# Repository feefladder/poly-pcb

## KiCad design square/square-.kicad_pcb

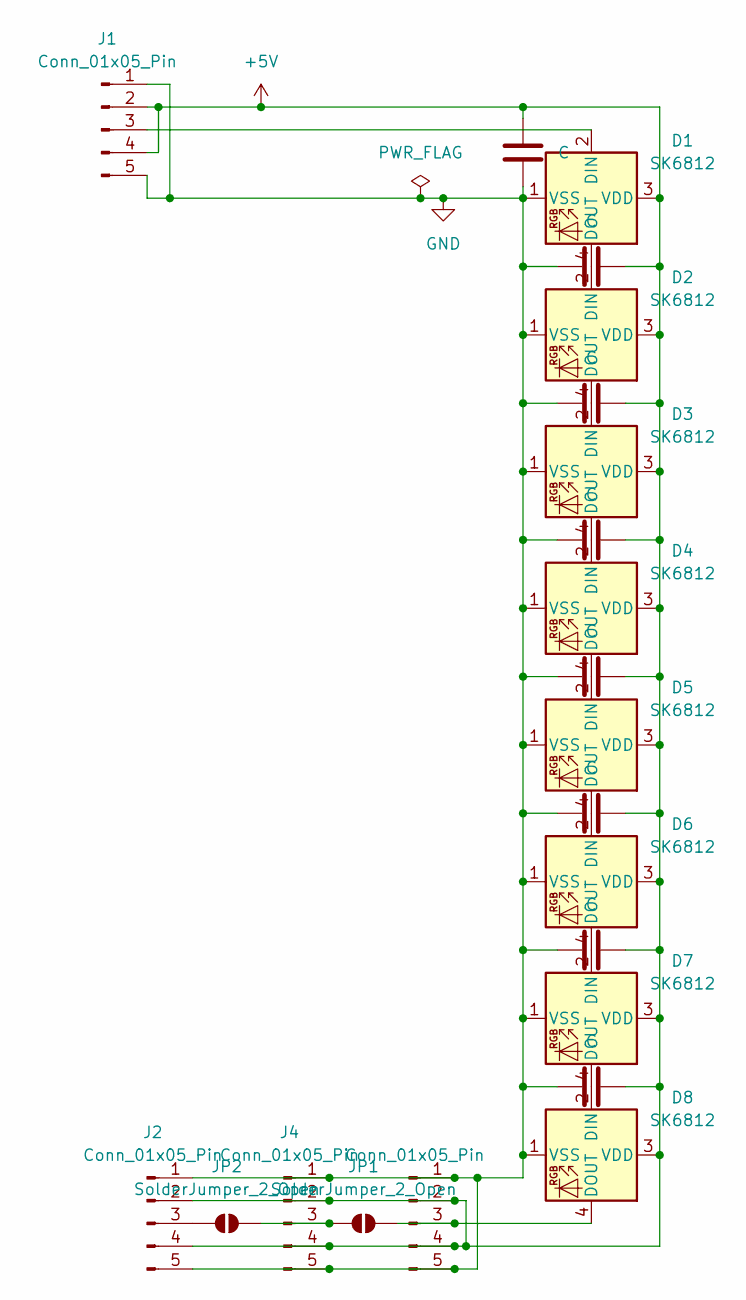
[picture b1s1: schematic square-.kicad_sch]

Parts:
C1, C2, C3, C4, C5, C6, C7, C8: C; C_0805_2012Metric_Pad1.18x1.45mm_HandSolder
D1, D2, D3, D4, D5, D6, D7, D8: SK6812; LED_SK6812_PLCC4_5.0x5.0mm_P3.2mm
J1, J2, J3, J4: Conn_01x05_Pin; PinHeader_1x05_P2.54mm_Vertical
JP1, JP2: SolderJumper_2_Open; SolderJumper-2_P1.3mm_Open_Pad1.0x1.5mm

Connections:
+5V: C1.2, C2.2, C3.2, C4.2, C5.2, C6.2, C7.2, C8.2, D1.3 (VDD), D2.3 (VDD), D3.3 (VDD), D4.3 (VDD), D5.3 (VDD), D6.3 (VDD), D7.3 (VDD), D8.3 (VDD), J1.2, J1.4, J2.2, J2.4, J3.2, J3.4, J4.2, J4.4
GND: C1.1, C2.1, C3.1, C4.1, C5.1, C6.1, C7.1, C8.1, D1.1 (VSS), D2.1 (VSS), D3.1 (VSS), D4.1 (VSS), D5.1 (VSS), D6.1 (VSS), D7.1 (VSS), D8.1 (VSS), J1.1, J1.5, J2.1, J2.5, J3.1, J3.5, J4.1, J4.5
unnamed: D1.2 (DIN), J1.3
unnamed: D1.4 (DOUT), D2.2 (DIN)
unnamed: D2.4 (DOUT), D3.2 (DIN)
unnamed: D3.4 (DOUT), D4.2 (DIN)
unnamed: D4.4 (DOUT), D5.2 (DIN)
unnamed: D5.4 (DOUT), D6.2 (DIN)
unnamed: D6.4 (DOUT), D7.2 (DIN)
unnamed: D7.4 (DOUT), D8.2 (DIN)
unnamed: D8.4 (DOUT), J3.3, JP1.2 (B)
unnamed: J2.3, JP2.1 (A)
unnamed: J4.3, JP1.1 (A), JP2.2 (B)

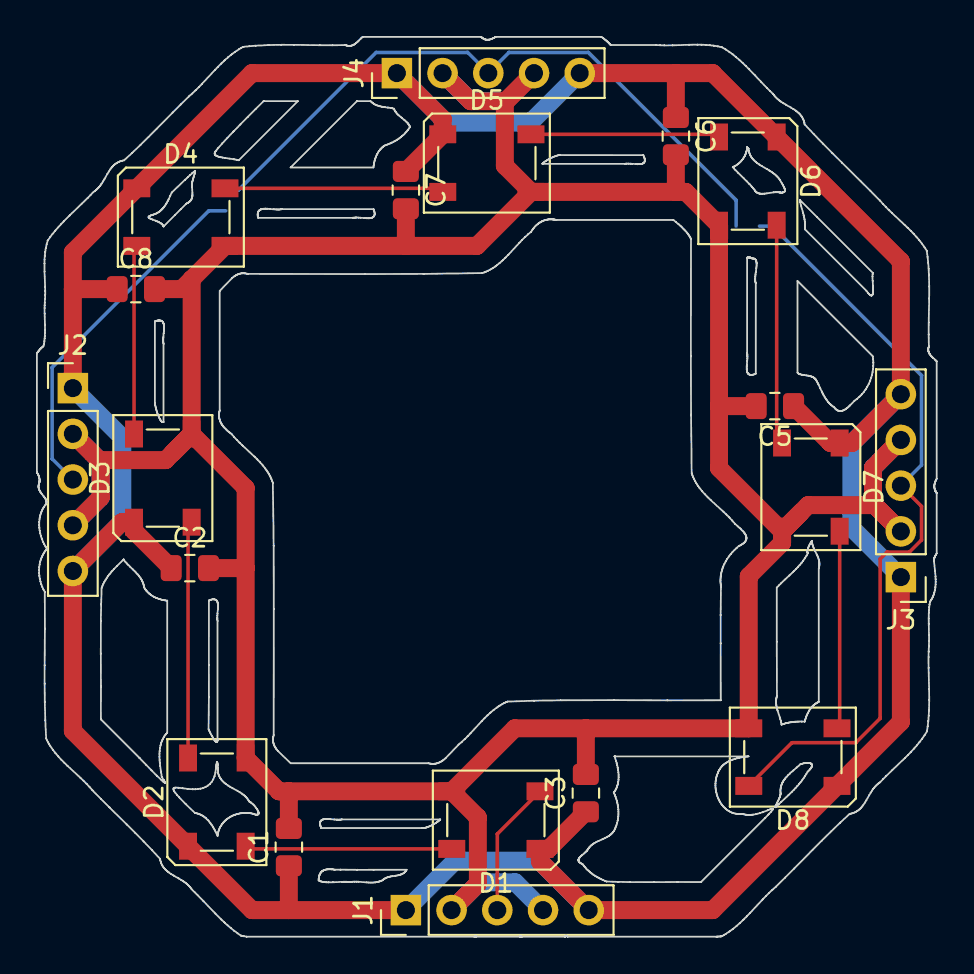
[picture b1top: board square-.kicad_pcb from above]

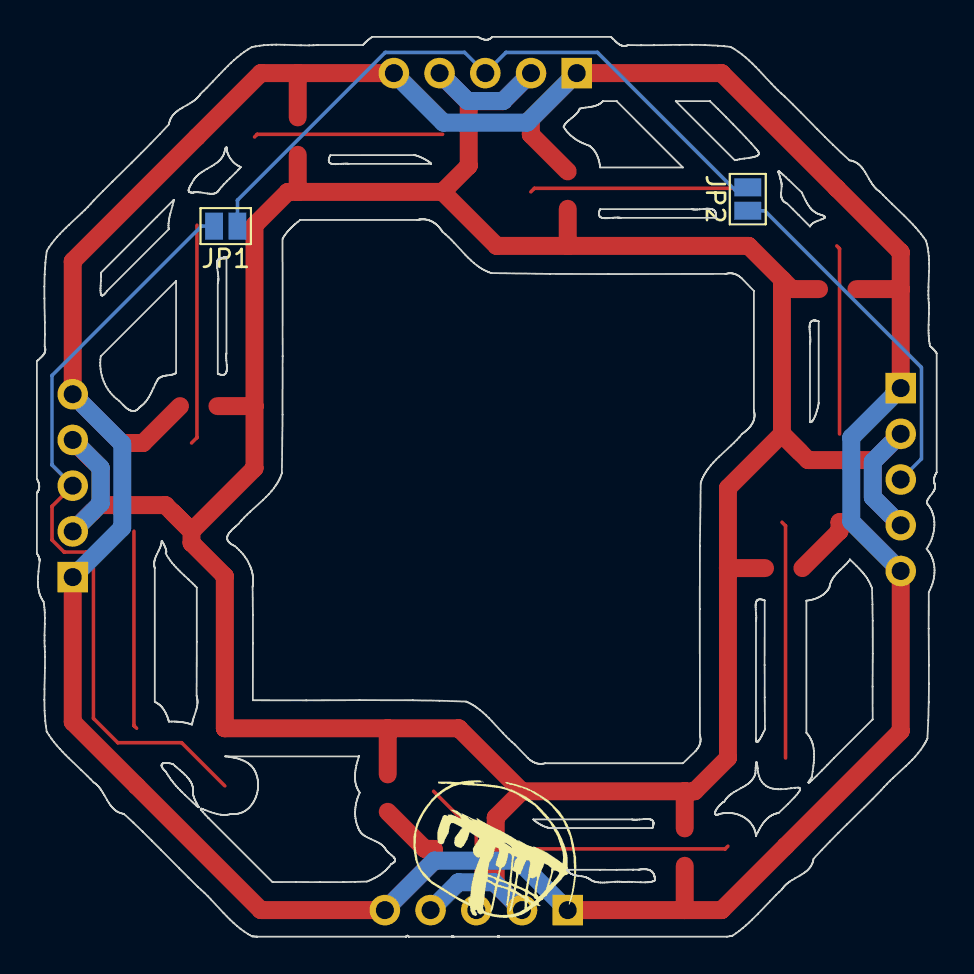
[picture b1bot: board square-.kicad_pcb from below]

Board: 2 copper layers, 50.0 x 50.0 mm, 21 parts (2 on the bottom side), 13 nets.

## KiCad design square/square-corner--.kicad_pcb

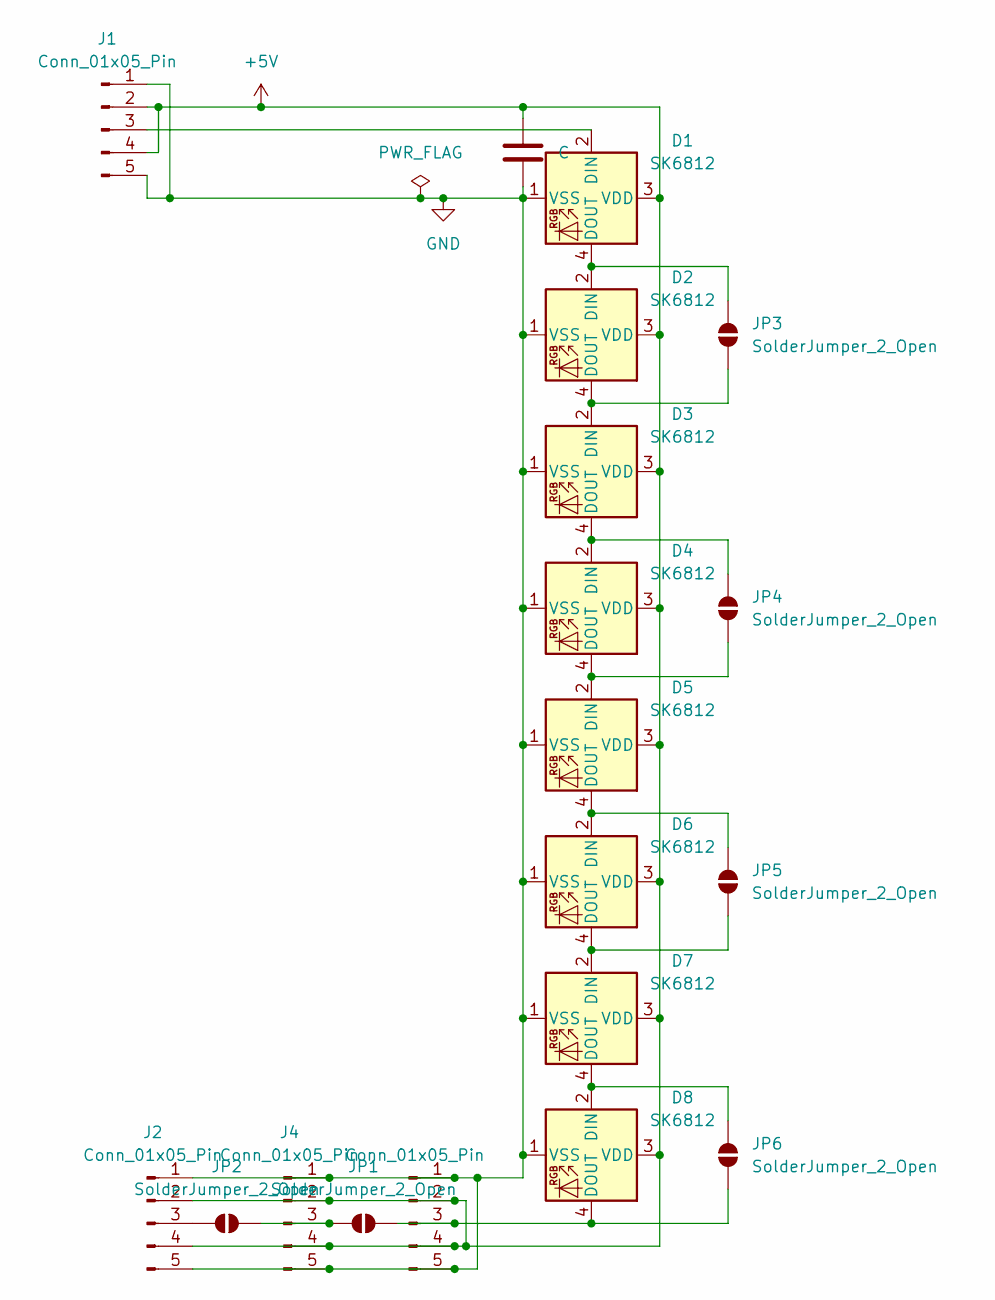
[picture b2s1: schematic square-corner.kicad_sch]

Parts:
C1: C; C_0805_2012Metric_Pad1.18x1.45mm_HandSolder
D1, D2, D3, D4, D5, D6, D7, D8: SK6812; LED_SK6812_PLCC4_5.0x5.0mm_P3.2mm
J1, J2, J3, J4: Conn_01x05_Pin; PinHeader_1x05_P2.54mm_Vertical
JP1, JP2: SolderJumper_2_Open; SolderJumper-2_P1.3mm_Open_Pad1.0x1.5mm
JP3, JP4, JP5, JP6: SolderJumper_2_Open; SolderJumper-2_P1.3mm_Open_RoundedPad1.0x1.5mm

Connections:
+5V: C1.2, D1.3 (VDD), D2.3 (VDD), D3.3 (VDD), D4.3 (VDD), D5.3 (VDD), D6.3 (VDD), D7.3 (VDD), D8.3 (VDD), J1.2, J1.4, J2.2, J2.4, J3.2, J3.4, J4.2, J4.4
GND: C1.1, D1.1 (VSS), D2.1 (VSS), D3.1 (VSS), D4.1 (VSS), D5.1 (VSS), D6.1 (VSS), D7.1 (VSS), D8.1 (VSS), J1.1, J1.5, J2.1, J2.5, J3.1, J3.5, J4.1, J4.5
unnamed: D1.2 (DIN), J1.3
unnamed: D1.4 (DOUT), D2.2 (DIN), JP3.2 (B)
unnamed: D2.4 (DOUT), D3.2 (DIN), JP3.1 (A)
unnamed: D3.4 (DOUT), D4.2 (DIN), JP4.2 (B)
unnamed: D4.4 (DOUT), D5.2 (DIN), JP4.1 (A)
unnamed: D5.4 (DOUT), D6.2 (DIN), JP5.2 (B)
unnamed: D6.4 (DOUT), D7.2 (DIN), JP5.1 (A)
unnamed: D7.4 (DOUT), D8.2 (DIN), JP6.2 (B)
unnamed: D8.4 (DOUT), J3.3, JP1.2 (B), JP6.1 (A)
unnamed: J2.3, JP2.1 (A)
unnamed: J4.3, JP1.1 (A), JP2.2 (B)

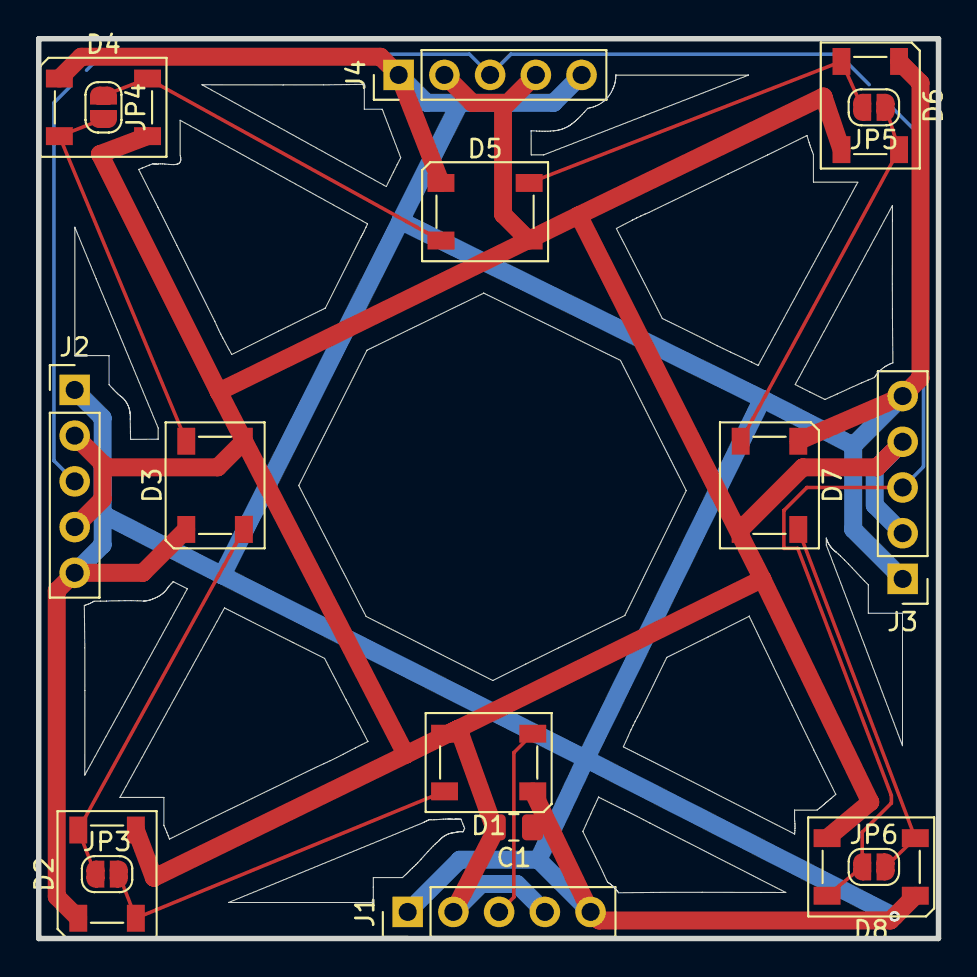
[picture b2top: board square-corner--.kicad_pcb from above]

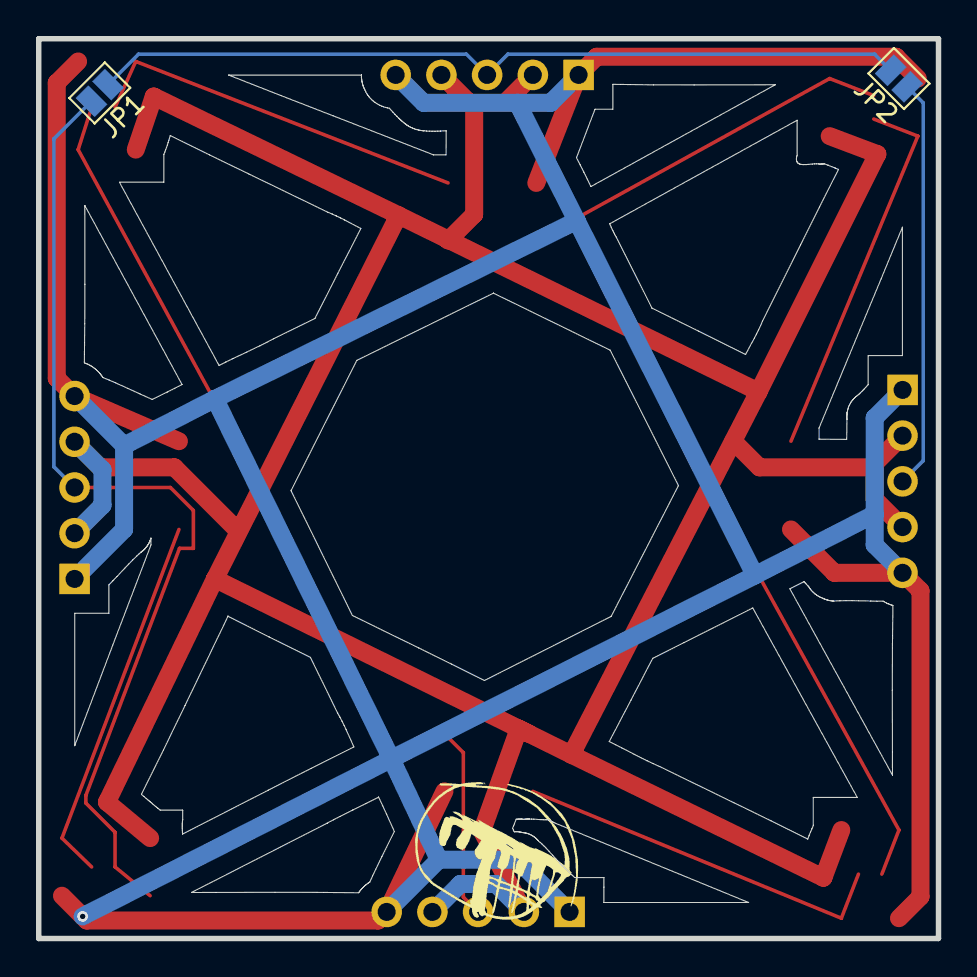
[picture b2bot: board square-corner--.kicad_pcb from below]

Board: 2 copper layers, 50.0 x 50.0 mm, 19 parts (2 on the bottom side), 13 nets.

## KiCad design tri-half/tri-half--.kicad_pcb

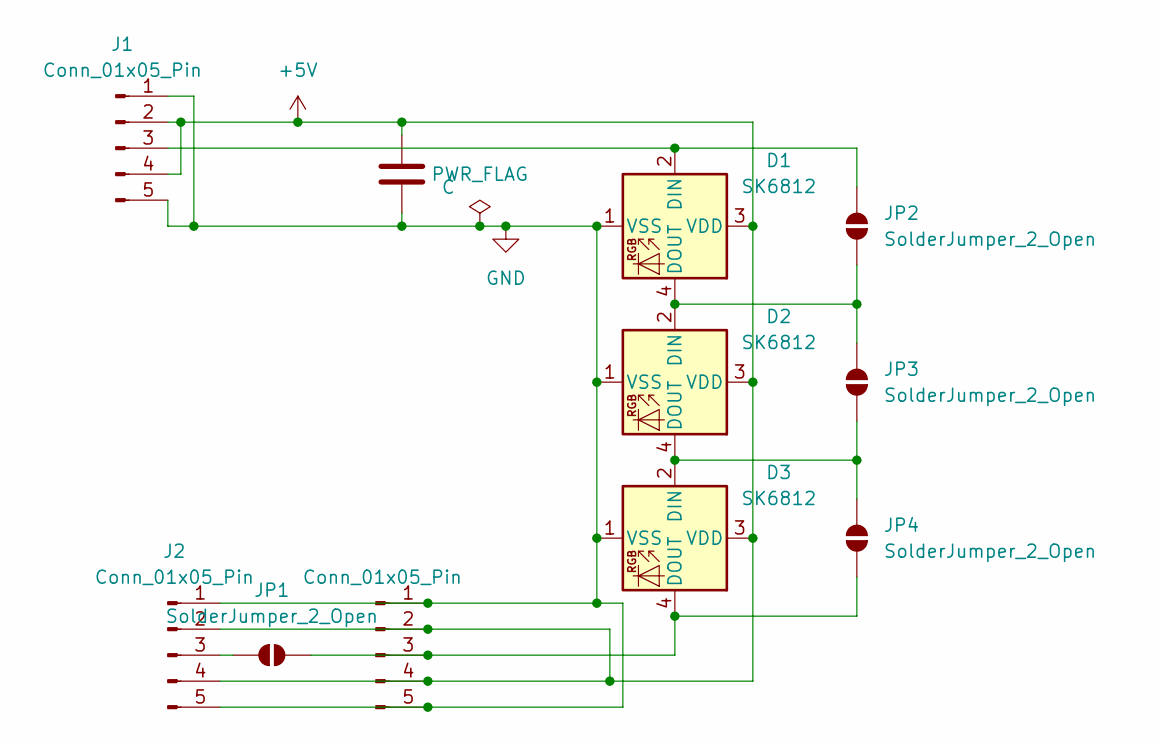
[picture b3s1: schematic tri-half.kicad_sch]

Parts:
C1: C; C_0805_2012Metric_Pad1.18x1.45mm_HandSolder
D1, D2, D3: SK6812; LED_SK6812_PLCC4_5.0x5.0mm_P3.2mm
J1, J2, J3: Conn_01x05_Pin; PinHeader_1x05_P2.54mm_Vertical
JP1: SolderJumper_2_Open; SolderJumper-2_P1.3mm_Open_Pad1.0x1.5mm
JP2, JP3, JP4: SolderJumper_2_Open; SolderJumper-2_P1.3mm_Open_RoundedPad1.0x1.5mm

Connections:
+5V: C1.1, D1.3 (VDD), D2.3 (VDD), D3.3 (VDD), J1.2, J1.4, J2.2, J2.4, J3.2, J3.4
GND: C1.2, D1.1 (VSS), D2.1 (VSS), D3.1 (VSS), J1.1, J1.5, J2.1, J2.5, J3.1, J3.5
unnamed: D1.2 (DIN), J1.3, JP2.2 (B)
unnamed: D1.4 (DOUT), D2.2 (DIN), JP2.1 (A), JP3.2 (B)
unnamed: D2.4 (DOUT), D3.2 (DIN), JP3.1 (A), JP4.2 (B)
unnamed: D3.4 (DOUT), J3.3, JP1.2 (B), JP4.1 (A)
unnamed: J2.3, JP1.1 (A)

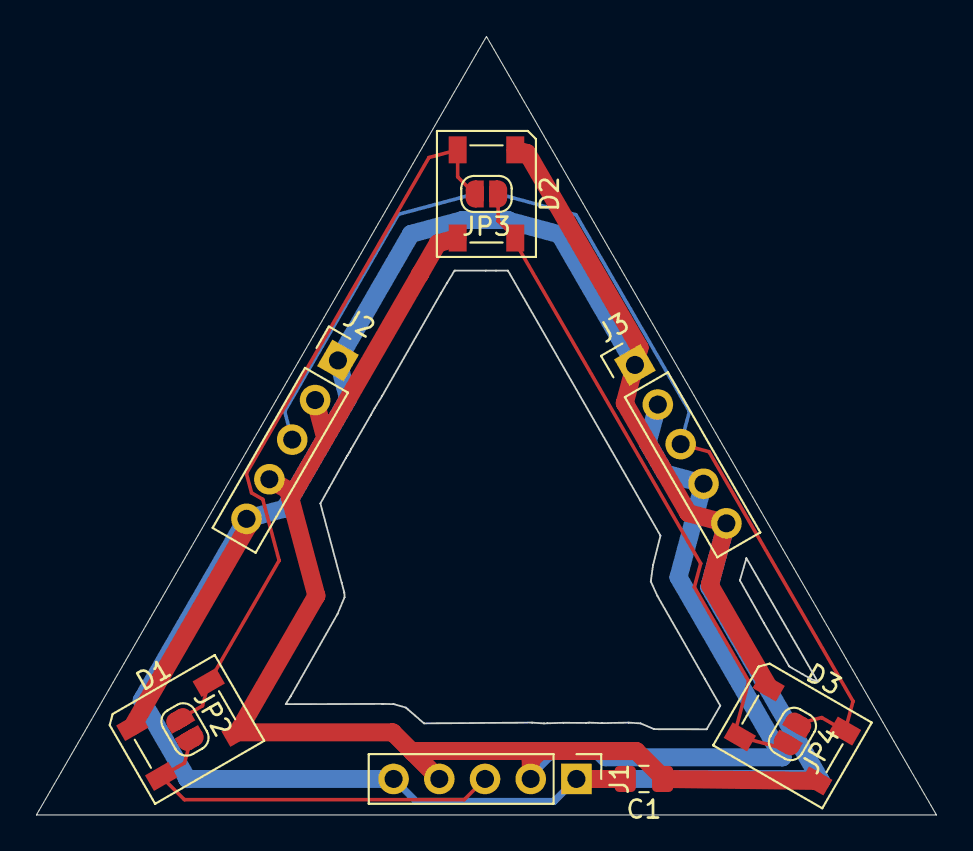
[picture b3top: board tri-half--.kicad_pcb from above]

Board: 2 copper layers, 50.0 x 43.3 mm, 11 parts (1 on the bottom side), 7 nets.

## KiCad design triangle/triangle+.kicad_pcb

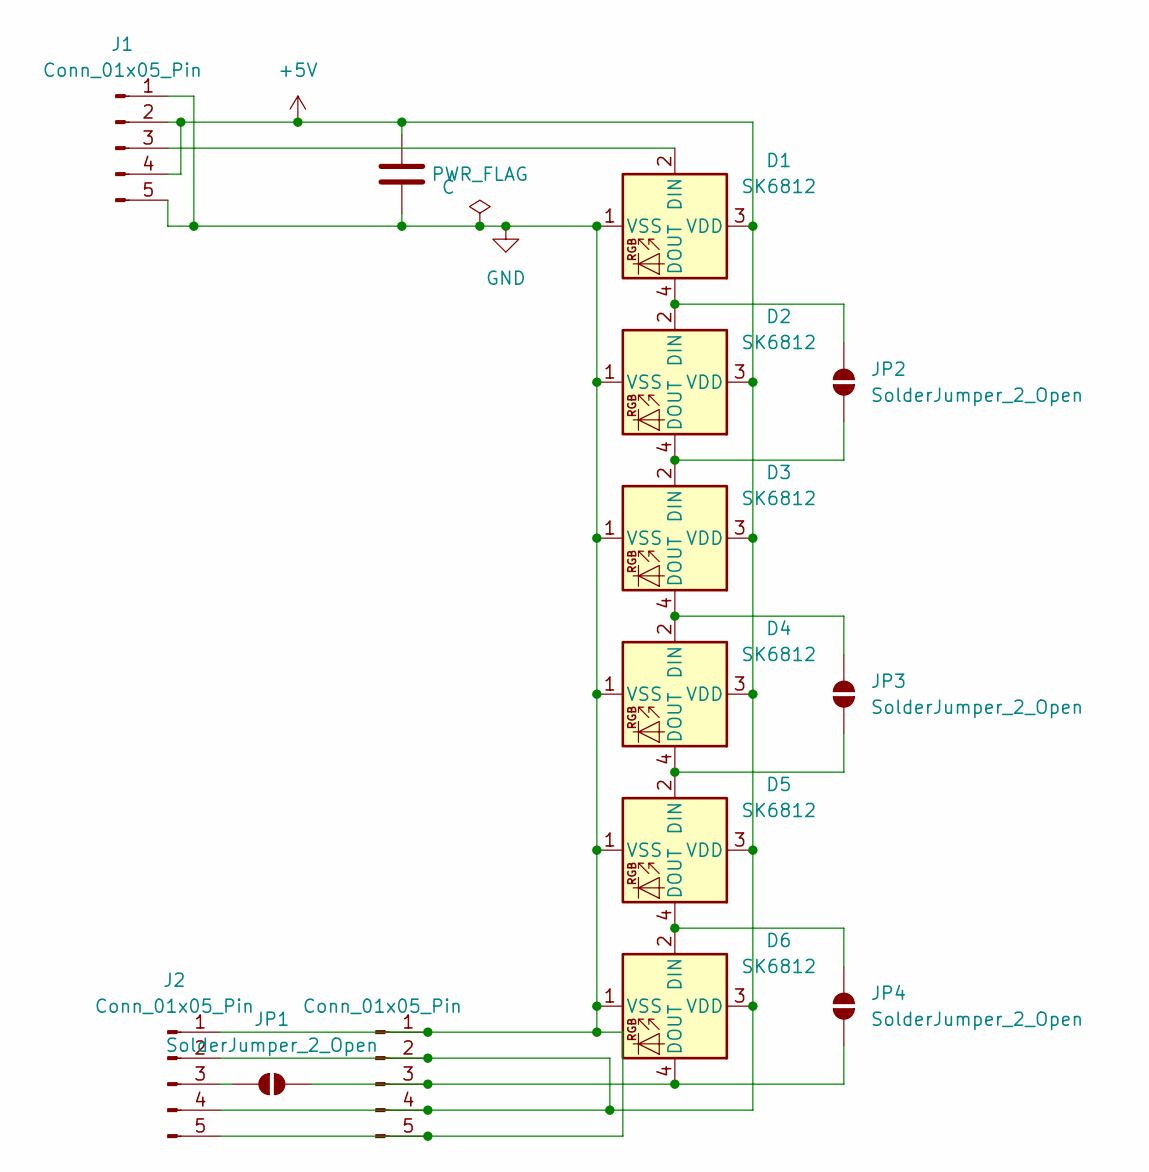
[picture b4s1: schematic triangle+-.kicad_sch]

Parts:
C1: C; C_0805_2012Metric_Pad1.18x1.45mm_HandSolder
D1, D2, D3, D4, D5, D6: SK6812; LED_SK6812_PLCC4_5.0x5.0mm_P3.2mm
J1, J2, J3: Conn_01x05_Pin; PinHeader_1x05_P2.54mm_Vertical
JP1: SolderJumper_2_Open; SolderJumper-2_P1.3mm_Open_Pad1.0x1.5mm
JP2, JP3, JP4: SolderJumper_2_Open; SolderJumper-2_P1.3mm_Open_RoundedPad1.0x1.5mm

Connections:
+5V: C1.1, D1.3 (VDD), D2.3 (VDD), D3.3 (VDD), D4.3 (VDD), D5.3 (VDD), D6.3 (VDD), J1.2, J1.4, J2.2, J2.4, J3.2, J3.4
GND: C1.2, D1.1 (VSS), D2.1 (VSS), D3.1 (VSS), D4.1 (VSS), D5.1 (VSS), D6.1 (VSS), J1.1, J1.5, J2.1, J2.5, J3.1, J3.5
unnamed: D1.2 (DIN), J1.3
unnamed: D1.4 (DOUT), D2.2 (DIN), JP2.2 (B)
unnamed: D2.4 (DOUT), D3.2 (DIN), JP2.1 (A)
unnamed: D3.4 (DOUT), D4.2 (DIN), JP3.2 (B)
unnamed: D4.4 (DOUT), D5.2 (DIN), JP3.1 (A)
unnamed: D5.4 (DOUT), D6.2 (DIN), JP4.2 (B)
unnamed: D6.4 (DOUT), J3.3, JP1.2 (B), JP4.1 (A)
unnamed: J2.3, JP1.1 (A)

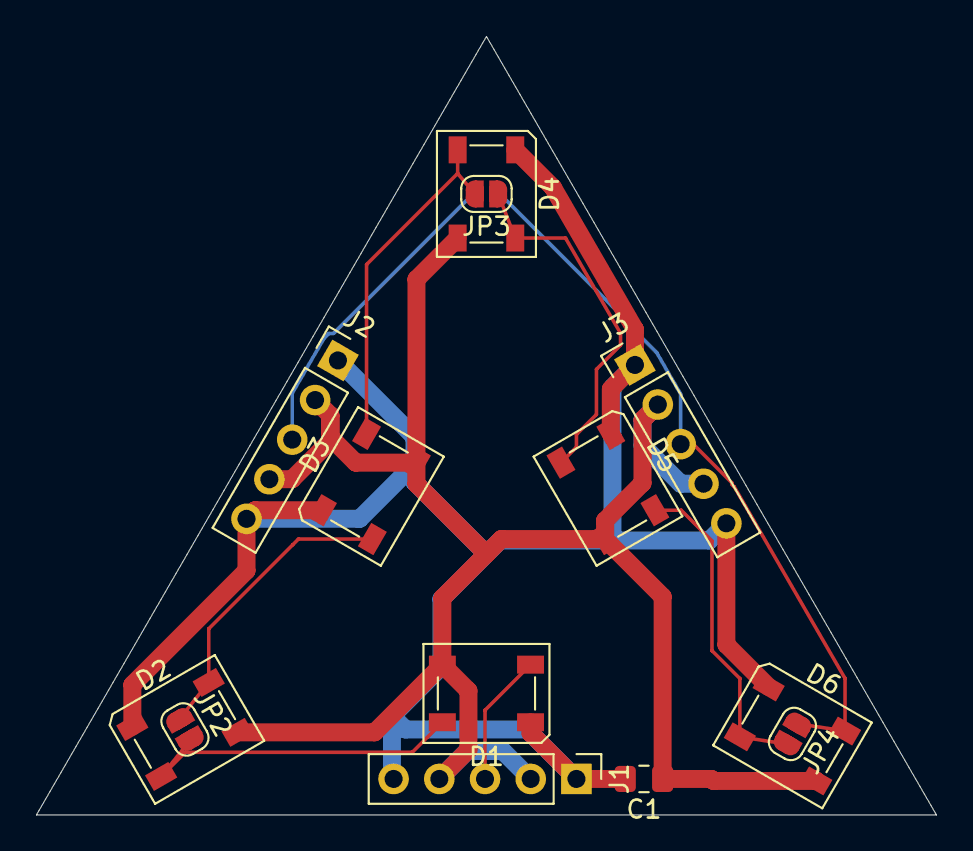
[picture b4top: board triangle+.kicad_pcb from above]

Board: 2 copper layers, 50.0 x 43.2 mm, 14 parts (1 on the bottom side), 10 nets.
